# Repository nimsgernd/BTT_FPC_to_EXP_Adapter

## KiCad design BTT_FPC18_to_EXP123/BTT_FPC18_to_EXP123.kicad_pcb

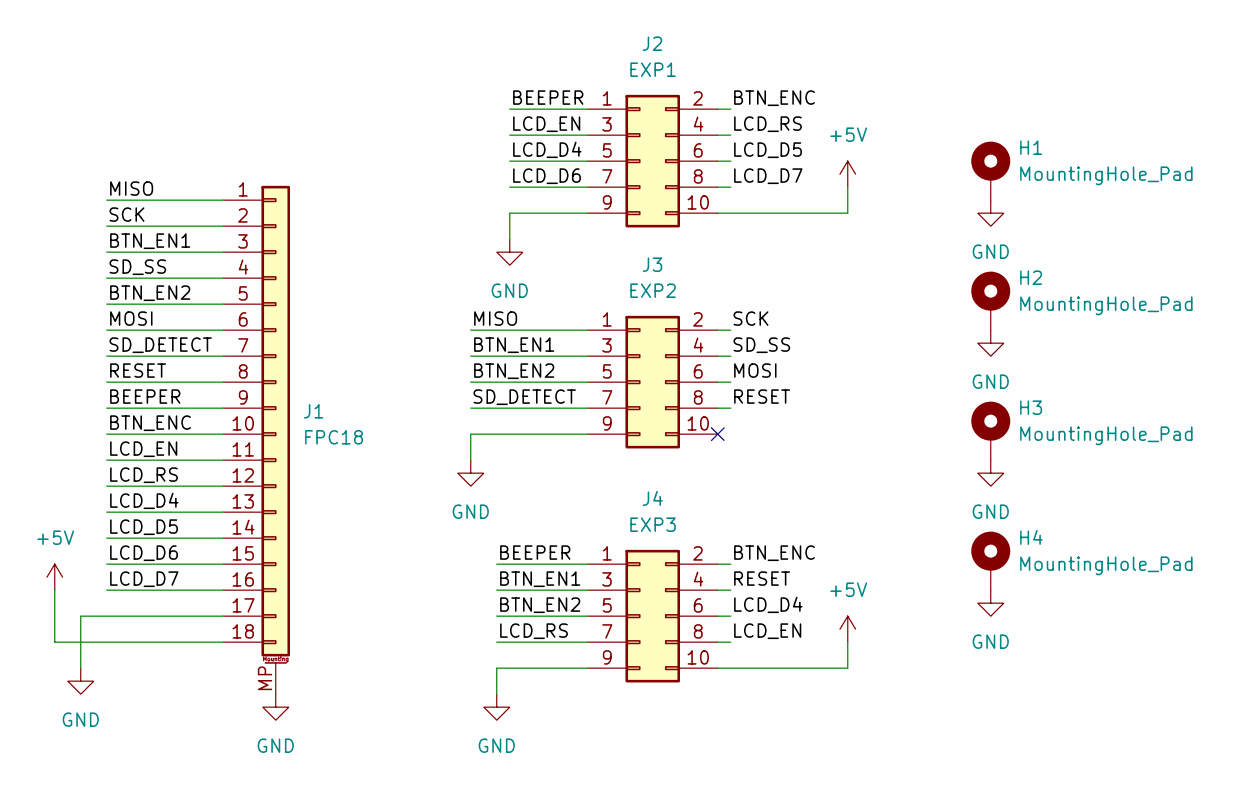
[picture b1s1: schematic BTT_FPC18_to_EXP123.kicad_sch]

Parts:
H1, H2, H3, H4: MountingHole_Pad; MountingHole_3.2mm_M3_DIN965_Pad
J1: FPC18; TE_1-84953-8_1x18-1MP_P1.0mm_Horizontal
J2: EXP1; IDC-Header_2x05_P2.54mm_Vertical
J3: EXP2; IDC-Header_2x05_P2.54mm_Vertical
J4: EXP3; IDC-Header_2x05_P2.54mm_Vertical

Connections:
+5V: J1.18, J2.10, J4.10
/BEEPER: J1.9, J2.1, J4.1
/BTN_EN1: J1.3, J3.3, J4.3
/BTN_EN2: J1.5, J3.5, J4.5
/BTN_ENC: J1.10, J2.2, J4.2
/LCD_D4: J1.13, J2.5, J4.6
/LCD_D5: J1.14, J2.6
/LCD_D6: J1.15, J2.7
/LCD_D7: J1.16, J2.8
/LCD_EN: J1.11, J2.3, J4.8
/LCD_RS: J1.12, J2.4, J4.7
/MISO: J1.1, J3.1
/MOSI: J1.6, J3.6
/RESET: J1.8, J3.8, J4.4
/SCK: J1.2, J3.2
/SD_DETECT: J1.7, J3.7
/SD_SS: J1.4, J3.4
GND: H1.1, H2.1, H3.1, H4.1, J1.17, J1.MP (MountPin), J2.9, J3.9, J4.9

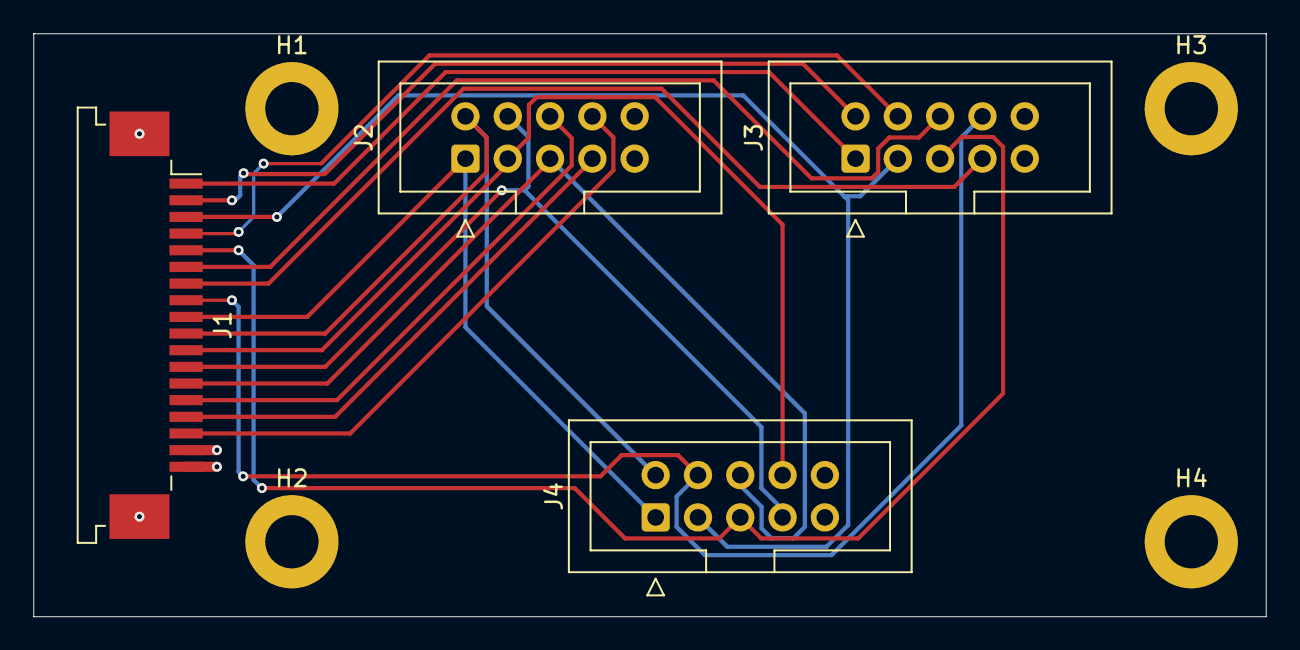
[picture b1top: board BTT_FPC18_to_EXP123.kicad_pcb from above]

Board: 4 copper layers, 74.0 x 35.0 mm, 8 parts (0 on the bottom side), 18 nets.

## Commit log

2024-11-12 Inital version of the adapter. I believe this version should work. I will keep refining it until I am confident to manufacture.
2025-04-07 Adjusted some trace routings
